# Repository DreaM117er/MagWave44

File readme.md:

# MagWave44

- 中文說明（Chinese Readme）。
- [英文說明（English Readme）](readme_en.md)。

## 簡介

Dactyl Manuform系列的鍵盤有很多種不同的樣式、也有各式各樣的作者製作成屬於自己的曲面分離式鍵盤，但大部分的Manuform系列根據的都是原始的模型再製而成，而這些成品也不一定適合自己的雙手。而在手指長度上，無名指是屬於比較特殊的一根手指，長度介於中指跟食指之間、又或者跟食指一樣長、而又或者比食指要短都有可能，這就導致大部分的鍵盤設計在無名指上不是那麼的友好。

而我本人的手屬於無名指長介於中指及食指之間，因此根據我的雙手及原始的Dactyl Manuform設計了第一把曲面分離式鍵盤，並且使用矮軸降低鍵盤的厚度，而這把鍵盤卻有著十分難操作移動手指的致命缺失。

於是我根據這個失敗的模型重新再設計了一個模型，以iPhone用戶的外殼配件Magsafe及波浪（Wave）狀的外殼底板，再根據44鍵的按鍵總數，將這把鍵盤取名為MagWave44。

- 第一把鍵盤模型。

- 我的左手手指長度。

## 材料清單

### 3D列印部件

|名稱|數量|備註|照片|
|---|---|---|---|
|底板|1組|左右手||
|定位板|1組|左右手||
|旋鈕定位板|1-2片|-||
|`D型`旋鈕帽|1-2個|-||

### 電路板

|名稱|數量|備註|正面|背面|
|---|---|---|---|---|
|單格電路板|42片|`矮軸`用|||
|TRRS專用電路板|2片|-|||
|EC-11的專用電路板|1-2片|-|||
|MCU電路板|2片|-|||
|本體電路板|2片|-|||

### 螺絲零件

|名稱|數量|備註|
|---|---|---|
|微型控制器|2片|規格請查詢下方`Note`|
|`1N4148` 二極體|42-44個|`DO-35`或`SOD-123`都可|
|`TRRS`座|2個|-|
|公母圓`排針`|-|-|
|`M2x5mm` 扁頭螺絲|78-84根|-|
|`M2x8mm` 扁頭螺絲|18根|可選配，有電路板才需要|
|`M2` 六角螺母|18個|可選配，有電路板才需要|
|`M2x5mm` 雙通銅柱|16根|-|
|`M2x7mm` 雙通銅柱|8根|-|
|`M2x10mm` 雙通銅柱|6根|旋鈕零件，可選配|
|`M2x12mm` 雙通銅柱|8根|-|
|`M2x18mm` 雙通銅柱|4根|-|
|`D型` `EC-11` 旋鈕編碼器|1-2個|`高15mm`，可選配|
|`M5x8mm` 以上厚頭螺絲|8根|Tending用，可選配|
|`M5` 六角螺母|8-14個|Tending用，可選配|
|`Magsafe`引磁圈或吸磁環|2個|Tending用，可選配|
|電線或漆包線|-|-|
|矮軸|42個|-|
|1u鍵帽|42個|-|

> **Note**
>
> 可使用的微型控制器請依據自身需求做選擇，因為是完全開源的關係，你可以任意變更目前使用的GPIO腳位，如果想要按照現有韌體組裝安裝鍵盤的話，以下微型控制器是我納入清單內的，供大家參考：
> 
> ATMega32U4系列：`ProMicro 5V16M`、`Eltie-C v4`。
> 
> RP2040系列：`RP2040-ProMicro`、`RP2040-Zero`、`RP2040-Matrix`、`RP2040-SuperMini`。

## 製作前準備

> **Note**
>
> MagWave44為3D列印的曲面鍵盤，由於定位板在設計上專屬於矮軸，螺絲配件屬於比較小的M2規格，推薦使用LCD或SLA的列印機製作。

> **Note**
>
> 推薦使用工程用樹脂進行列印，確保鍵盤部件不會輕易斷裂及融化。

> **Note**
>
> 鍵盤韌體有4種可供選用，製作方式會以降低手拉線的難易度去介紹。

> **Warning**
>
> 個人操作3D列印機、使用電烙鐵工具等務必注意環境通風，避免中毒、火源、燒燙傷等危險。

- [點我進入組裝說明](guide.md)。

## 鍵盤配列

## 參考及使用資料
- [QMK Firmware](https://qmk.fm/).
- [VIAL](https://get.vial.today/).
- [KiCAD](https://www.kicad.org/) version `7.0.5.`
- [JLCPCB](https://jlcpcb.com/).
- [DeepL](https://www.deepl.com/translator).
- [AutoDesk Fusion360](https://www.autodesk.com/products/fusion-360/free-trial).

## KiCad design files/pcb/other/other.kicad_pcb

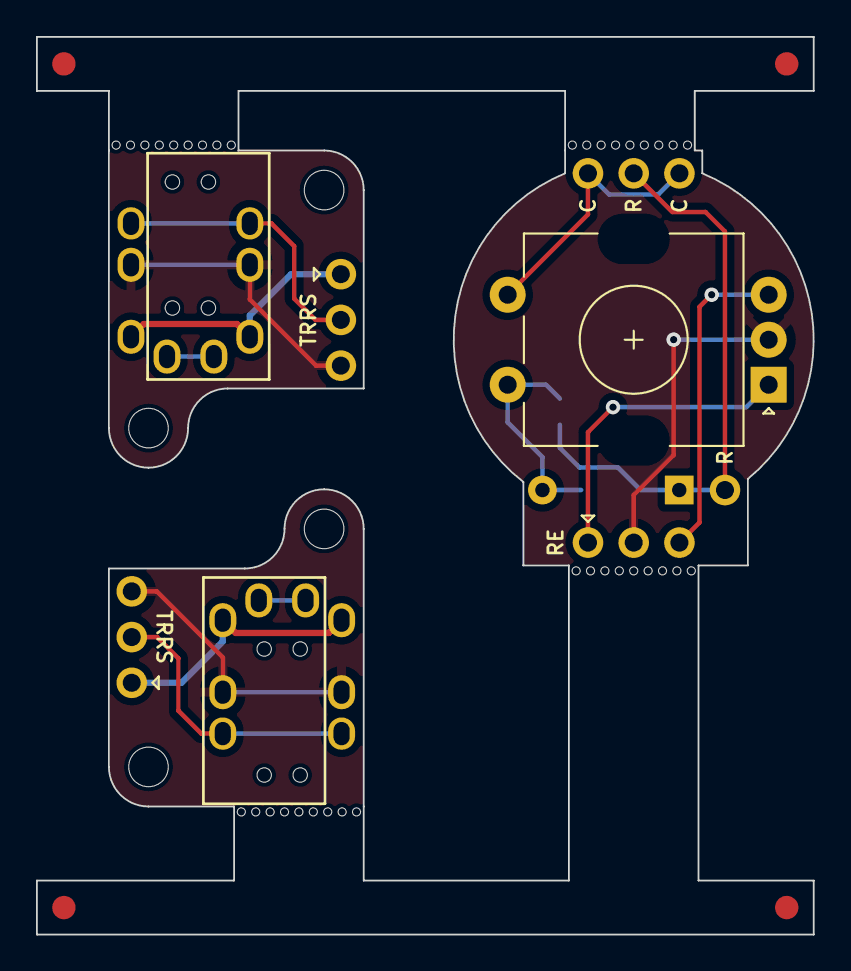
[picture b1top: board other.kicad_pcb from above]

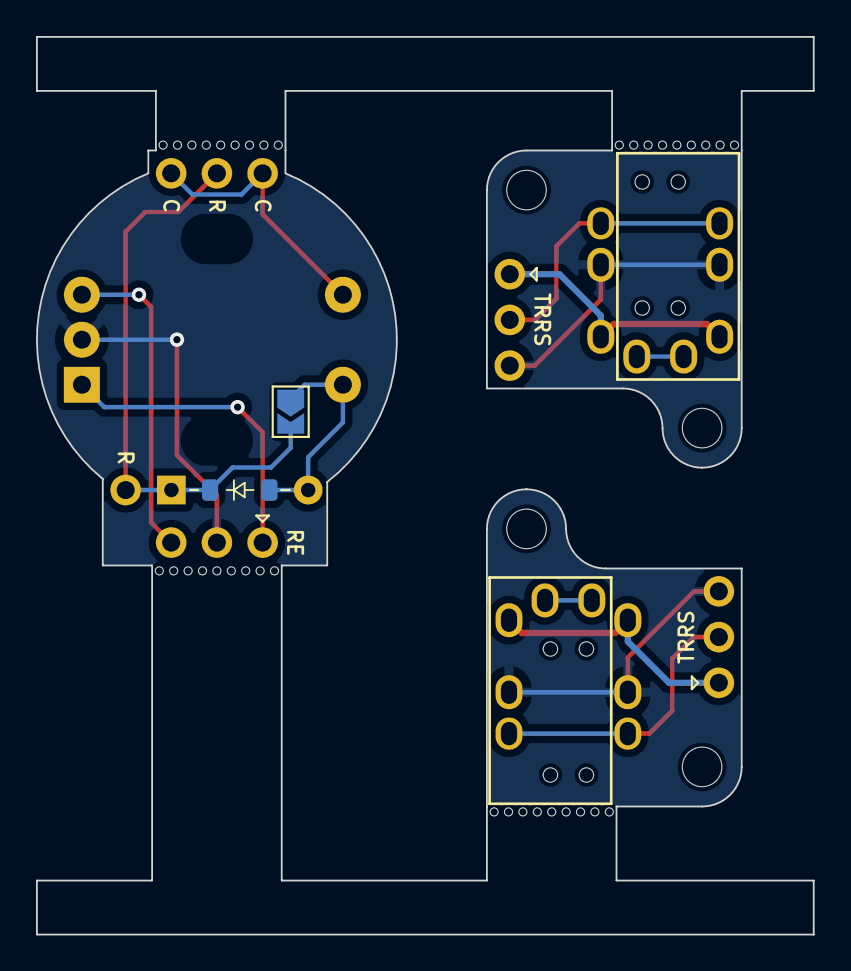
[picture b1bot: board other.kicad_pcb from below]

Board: 2 copper layers, 43.2 x 49.9 mm, 22 parts (3 on the bottom side), 8 nets.

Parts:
D1: 1N4148_TS; D_DO-35_SOD27_P7.62mm_Horizontal
H1, H1#2, H2, H2#2: M2; MountingHole_2.2mm_M2
H3, H7, H8, H9: edge; Breakaway_Tabs
H10, H13, H14, H15: tooling hole; tooling_hole
J1, J1#2: LTRRS; PinHeader_1x03_P2.54mm_Vertical
J10: row; PinHeader_1x01_P2.54mm_Vertical
J11: EC-11; PinHeader_1x03_P2.54mm_Vertical
J12: col; PinHeader_1x03_P2.54mm_Vertical
JP1: JUMPER; SolderJumper-2_P1.3mm_Open_TrianglePad1.0x1.5mm
RE1: 1; RotaryEncoder_EC11
T1, T1#2: AudioJack4; TRRS-PJ-320A, dual side x2

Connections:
5V1: J1.1, J1#2.1, T1.1 (T/VCC), T1#2.1 (T/VCC)
GND: J1.3, J1#2.3, J11.2, RE1.C (GND), T1.3 (R/GND), T1#2.3 (R/GND)
LA11: J11.1, RE1.A (CLK)
LB11: J11.3, RE1.B (DT)
LTRRS: J1.2, J1#2.2, T1.2 (R/SNL), T1#2.2 (R/SNL)
unnamed: D1.2, JP1.1, RE1.S2 (SW)
col_re: J12.1, J12.3, RE1.S1 (GND)
row_re: D1.1, J10.1, J12.2, JP1.2

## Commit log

2024-01-17 update files
2024-01-17 update pcb
2024-01-18 update new pics
2024-01-18 update building guide
2024-01-18 update guide
2024-01-23 rename keyboard name
2024-01-24 renew files and pics
2024-01-24 update layout pics
2024-01-24 update keymap pics
2024-01-26 fix the building list
2024-01-26 renew keymap layers
